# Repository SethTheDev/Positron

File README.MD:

# Resonance
An open-source USB-C Audio Interface powered by an STM32F411 and using a Cirrus Logic CS43198 DAC chip.

This is my magnum opus (*seriously*)

## Features
* STM32F411 microcontroller for USB audio
* Cirrus Logic CS43198 DAC with pseudo-differential output
* OPA1622 Differential Headphone Amplifier

## Rough Timeline
* (May 2026) - Raspberry Pi Pico + PCM5102

* (August 2026) - Stuck with the Pico because of it's versatility, however I decided to use a professional Cirrus Logic CS43198 chip
* (September 2026) - Switch to an STM32H743 (way too overpowered, what was I thinking), and included a CS5361 ADC with dual-channel op-amps for two mic inputs

* (October 2026) - Realized I would face a lot of power-related problems so I downgraded to an STM32F411 and kept only the CS43198 DAC. Also completely revamped the schematic so it would be easy to read

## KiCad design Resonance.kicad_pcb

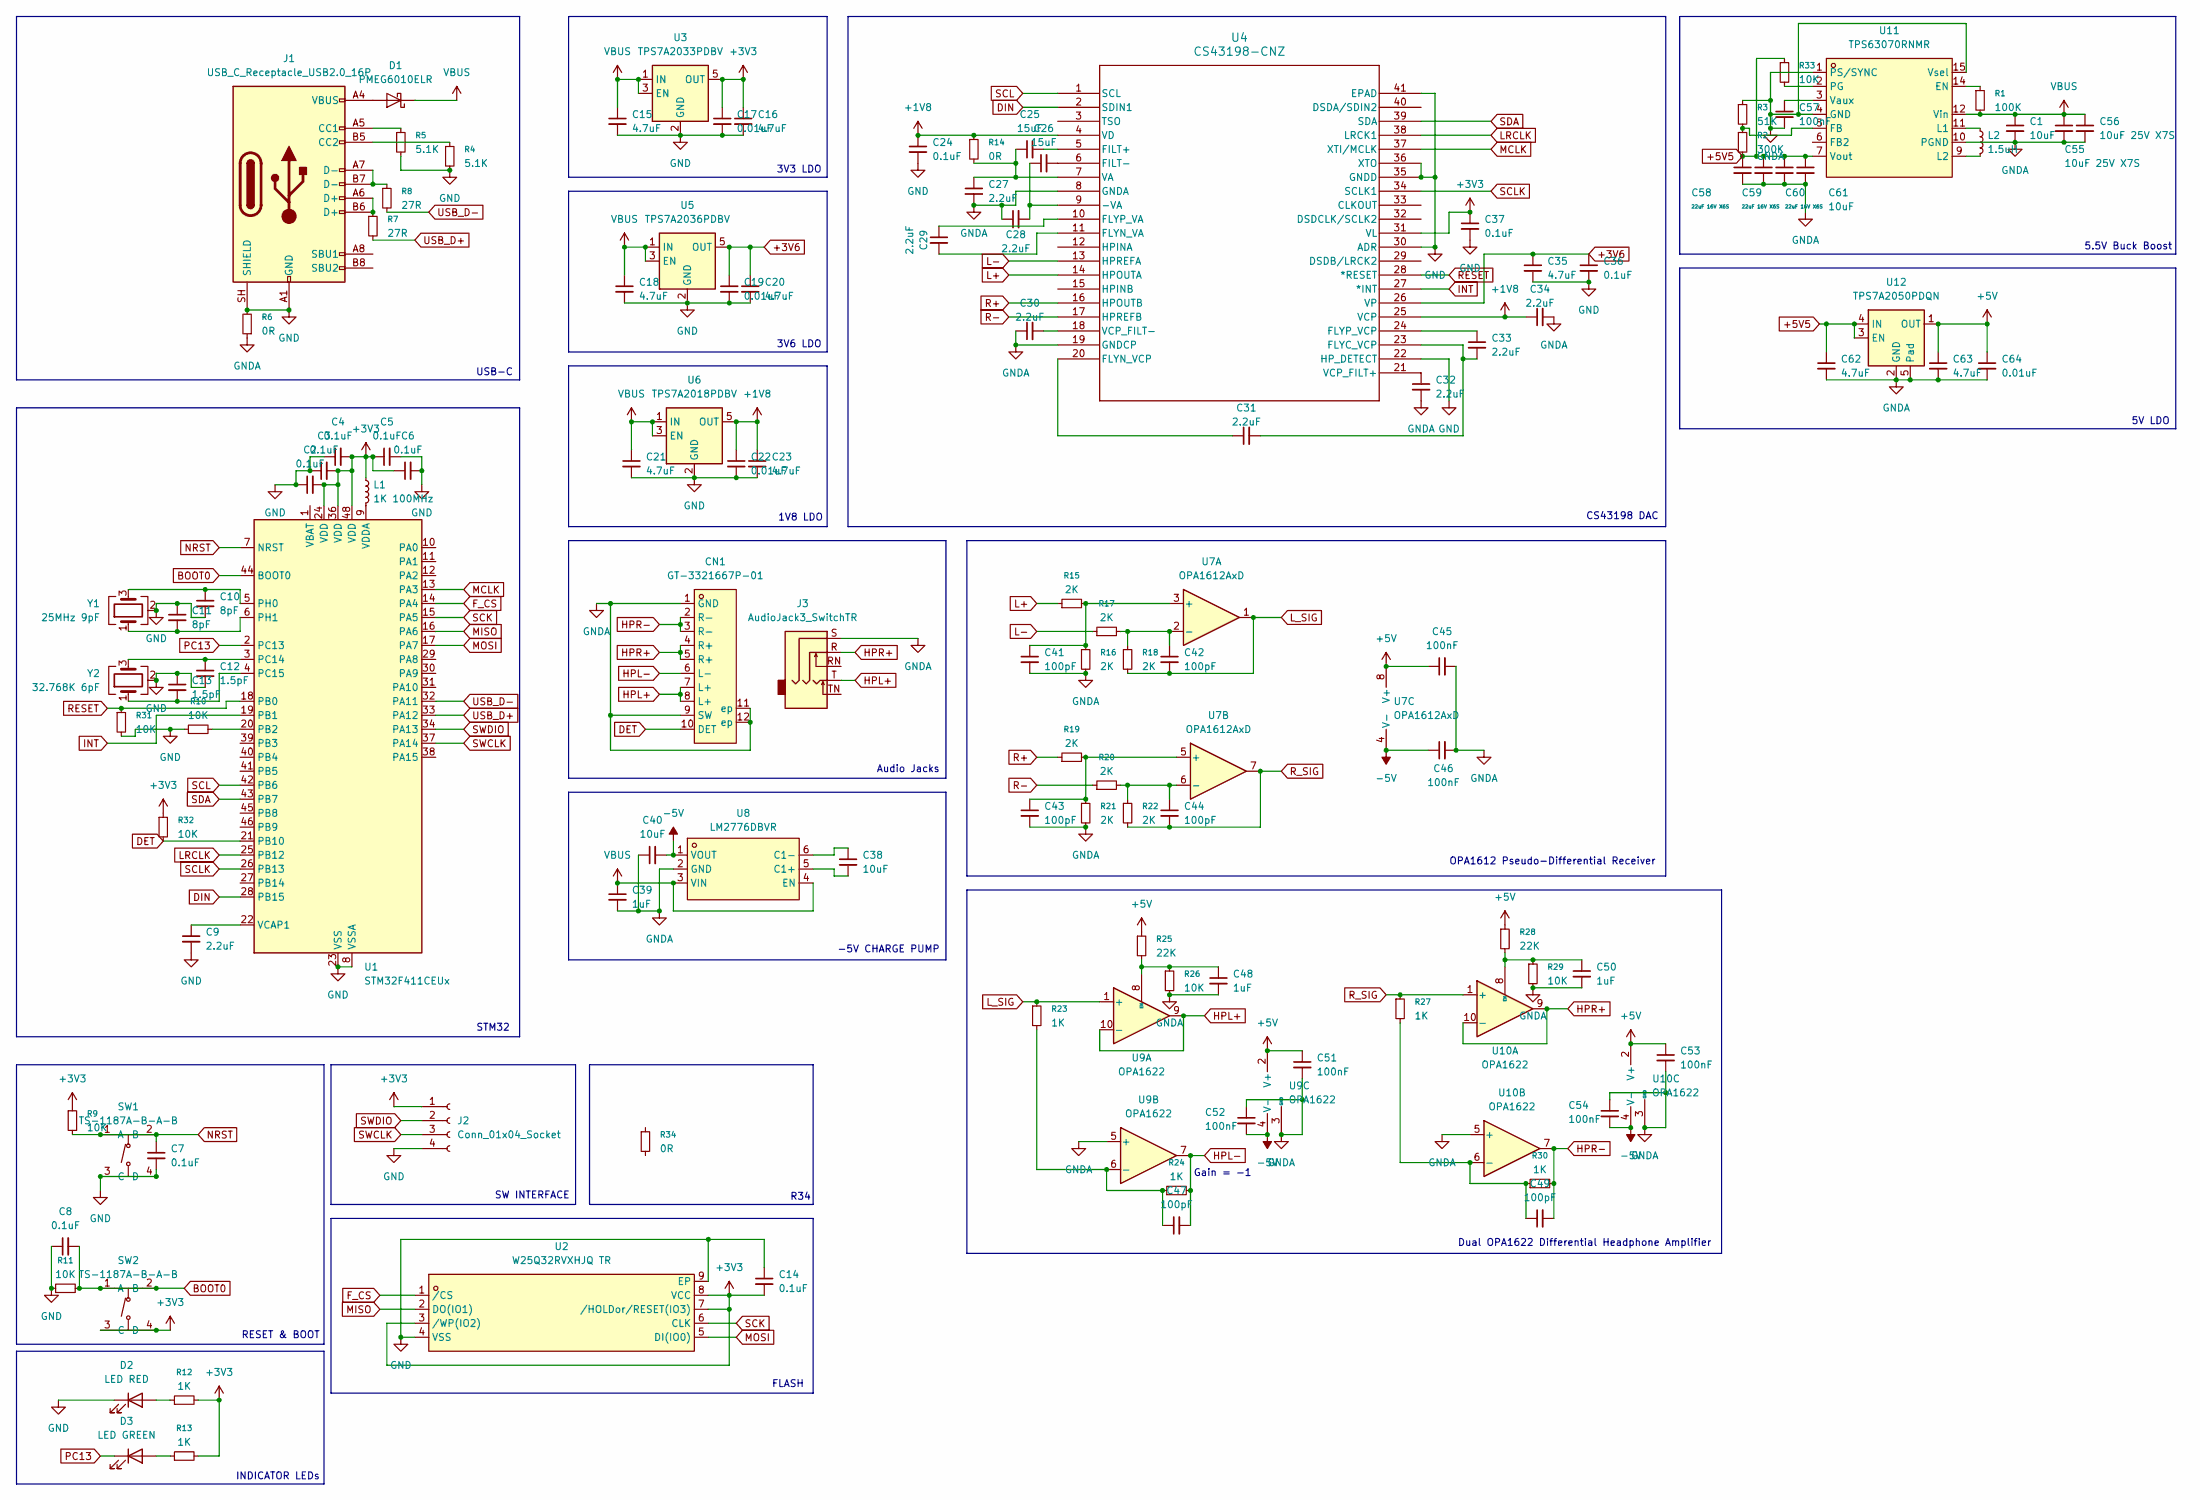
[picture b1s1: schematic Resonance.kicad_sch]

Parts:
C1, C61: 10uF; C_0603_1608Metric
C2, C3, C4, C5, C6, C7, C8, C14, C24, C36, C37: 0.1uF; C_0402_1005Metric
C9, C27, C28, C29, C30, C31, C32, C33, C34: 2.2uF; C_0402_1005Metric
C10, C11: 8pF; C_0402_1005Metric
C12, C13: 1.5pF; C_0402_1005Metric
C15, C16, C18, C20, C21, C23, C35, C62, C63: 4.7uF; C_0402_1005Metric
C17, C19, C22, C64: 0.01uF; C_0402_1005Metric
C25, C26: 15uF; C_0402_1005Metric
C38, C40: 10uF; C_0402_1005Metric
C39, C48, C50: 1uF; C_0402_1005Metric
C41, C42, C43, C44, C47, C49: 100pF; C_0402_1005Metric
C45, C46, C51, C52, C53, C54, C57: 100nF; C_0402_1005Metric
C55, C56: 10uF 25V X7S; C_0805_2012Metric
C58, C59, C60: 22uF 16V X6S; C_0805_2012Metric
CN1: GT-3321667P-01; AUDIO-TH_GT-3321667P-01; MPN GT-3321667P-01; LCSC Part C2762984
D1: PMEG6010ELR; Nexperia_CFP3_SOD-123W
D2: LED RED; LED_0805_2012Metric
D3: LED GREEN; LED_0805_2012Metric
J1: USB_C_Receptacle_USB2.0_16P; USB_C_Receptacle_GCT_USB4105-xx-A_16P_TopMnt_Horizontal
J2: Conn_01x04_Socket; PinSocket_1x04_P2.54mm_Vertical
J3: AudioJack3_SwitchTR; Jack_3.5mm_CUI_SJ1-3525N_Horizontal
L1: 1K 100MHz; L_0402_1005Metric
L2: 1.5uH; L_0402_1005Metric
R1: 100K; R_0402_1005Metric
R2: 300K; R_0402_1005Metric
R3: 51K; R_0402_1005Metric
R4, R5: 5.1K; R_0402_1005Metric
R6, R14, R34: 0R; R_0402_1005Metric
R7, R8: 27R; R_0402_1005Metric
R9, R10, R11, R26, R29, R31, R32, R33: 10K; R_0402_1005Metric
R12, R13, R23, R24, R27, R30: 1K; R_0402_1005Metric
R15, R16, R17, R18, R19, R20, R21, R22: 2K; R_0402_1005Metric
R25, R28: 22K; R_0402_1005Metric
SW1, SW2: TS-1187A-B-A-B; SW-SMD_4P-L5.1-W5.1-P3.70-LS6.5-TL_H1.5; MPN TS-1187A-B-A-B; LCSC Part C318884
U1: STM32F411CEUx; QFN-48-1EP_7x7mm_P0.5mm_EP5.6x5.6mm
U2: W25Q32RVXHJQ TR; USON-8_L3.0-W2.0-P0.50-BL-EP; MPN W25Q32RVXHJQ TR; LCSC Part C32246052
U3: TPS7A2033PDBV; SOT-23-5
U4: CS43198-CNZ; QFN_CS43198_CIR-M
U5: TPS7A2036PDBV; SOT-23-5
U6: TPS7A2018PDBV; SOT-23-5
U7: OPA1612AxD; SOIC-8_3.9x4.9mm_P1.27mm
U8: LM2776DBVR; SOT-23-6_L2.9-W1.6-P0.95-LS2.8-BR; MPN LM2776DBVR; LCSC Part C69527
U9, U10: OPA1622; Texas_S-PVSON-N10
U11: TPS63070RNMR; VQFN-15_L3.0-W2.5-P0.50-BL; MPN TPS63070RNMR; LCSC Part C109322
U12: TPS7A2050PDQN; Texas_X2SON-4_1x1mm_P0.65mm
Y1: 25MHz 9pF; Crystal_SMD_3225-4Pin_3.2x2.5mm
Y2: 32.768K 6pF; Crystal_SMD_3225-4Pin_3.2x2.5mm

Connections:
+1V8: C22.1, C23.1, C24.1, C34.1, R14.1, U4.4 (VD), U4.25 (VCP), U6.5 (OUT)
+3V3: C2.2, C3.2, C4.2, C5.1, C6.1, C14.2, C16.1, C17.1, C37.1, J2.1, L1.1, R9.1, R12.2, R13.2, R32.1, SW2.3 (C), SW2.4 (D), U1.24 (VDD), U1.36 (VDD), U1.48 (VDD), U2.3 (/WP(IO2)), U2.7 (/HOLDor/RESET(IO3)), U2.8 (VCC), U3.5 (OUT), U4.31 (VL)
+3V6: C19.1, C20.1, C35.1, C36.1, U4.26 (VP), U5.5 (OUT)
+5V: C45.1, C51.1, C53.1, C63.1, C64.1, R25.1, R28.1, U7.8 (V+), U9.2 (V+), U10.2 (V+), U12.1 (OUT)
+5V5: C58.1, C59.1, C60.1, C61.1, C62.1, R2.2, R33.1, U11.7 (Vout), U12.3 (EN), U12.4 (IN)
-5V: C40.2, C46.1, C52.2, C54.2, U7.4 (V-), U8.1 (VOUT), U9.4 (V-), U9.11 (V-), U10.4 (V-), U10.11 (V-)
BOOT0: C8.2, R11.2, SW2.1 (A), SW2.2 (B), U1.44 (BOOT0)
DET: CN1.10 (DET), R32.2, U1.21 (PB10)
DIN: U1.28 (PB15), U4.2 (SDIN1)
F_CS: U1.14 (PA4), U2.1 (/CS)
GND: C2.1, C3.1, C4.1, C5.2, C6.2, C7.2, C8.1, C9.2, C10.2, C11.1, C12.2, C13.1, C14.1, C15.2, C16.2, C17.2, C18.2, C19.2, C20.2, C21.2, C22.2, C23.2, C24.2, C35.2, C36.2, C37.2, D2.1 (K), J1.A1 (GND), J1.A12 (GND), J1.B1 (GND), J1.B12 (GND), J1.SH (SHIELD), J2.4, R4.2, R5.2, R6.2, R10.1, R11.1, R31.2, SW1.3 (C), SW1.4 (D), U1.8 (VSSA), U1.23 (VSS), U1.35 (VSS), U1.47 (VSS), U1.49 (VSS), U2.4 (VSS), U2.9 (EP), U3.2 (GND), U4.22 (HP_DETECT), U4.30 (ADR), U4.35 (GNDD), U4.36 (XTO), U4.41 (EPAD), U5.2 (GND), U6.2 (GND), Y1.2 (G), Y1.4 (G), Y2.2 (G), Y2.4 (G)
GNDA: C1.2, C27.2, C28.1, C30.1, C32.2, C34.2, C39.2, C40.1, C41.2, C43.2, C45.2, C46.2, C48.2, C50.2, C51.2, C52.1, C53.2, C54.1, C55.2, C56.2, C57.2, C58.2, C59.2, C60.2, C61.2, C62.2, C63.2, C64.2, CN1.1 (GND), CN1.9 (SW), CN1.11 (ep), CN1.12 (ep), J3.S, R3.1, R6.1, R16.2, R21.2, R26.2, R29.2, U4.8 (GNDA), U4.19 (GNDCP), U8.2 (GND), U9.3 (GND), U9.5 (+), U10.3 (GND), U10.5 (+), U11.1 (PS/SYNC), U11.4 (GND), U11.10 (PGND), U11.15 (Vsel), U12.2 (GND), U12.5 (Pad)
HPL+: CN1.7 (L+), CN1.8 (L+), J3.T, U9.9, U9.10 (-)
HPL-: C47.2, CN1.6 (L-), R24.2, U9.7
HPR+: CN1.4 (R+), CN1.5 (R+), J3.R, U10.9, U10.10 (-)
HPR-: C49.2, CN1.2 (R-), CN1.3 (R-), R30.2, U10.7
INT: U1.19 (PB1), U4.27 (*INT)
L+: R15.1, U4.14 (HPOUTA)
L-: R17.1, U4.13 (HPREFA)
LRCLK: U1.25 (PB12), U4.38 (LRCK1)
L_SIG: C42.2, R18.2, R23.1, U7.1, U9.1 (+)
MCLK: U1.13 (PA3), U4.37 (XTI/MCLK)
MISO: U1.16 (PA6), U2.2 (DO(IO1))
MOSI: U1.17 (PA7), U2.5 (DI(IO0))
NRST: C7.1, R9.2, SW1.1 (A), SW1.2 (B), U1.7 (NRST)
unnamed: D1.2 (A), J1.A4 (VBUS), J1.A9 (VBUS), J1.B4 (VBUS), J1.B9 (VBUS)
unnamed: D2.2 (A), R12.1
unnamed: D3.2 (A), R13.1
unnamed: J1.A5 (CC1), R5.1
unnamed: J1.B5 (CC2), R4.1
unnamed: J1.A6 (D+), J1.B6 (D+), R7.1
unnamed: J1.A7 (D-), J1.B7 (D-), R8.1
unnamed: R10.2, U1.20 (PB2)
unnamed: C12.1, U1.3 (PC14), Y2.3
unnamed: C13.2, U1.4 (PC15), Y2.1
unnamed: C10.1, U1.5 (PH0), Y1.3
unnamed: C11.2, U1.6 (PH1), Y1.1
unnamed: C9.1, U1.22 (VCAP1)
unnamed: L1.2, U1.9 (VDDA)
unnamed: C26.1, C28.2, U4.9 (-VA)
unnamed: C25.2, U4.5 (FILT+)
unnamed: C26.2, U4.6 (FILT-)
unnamed: C31.2, C33.2, U4.23 (FLYC_VCP)
unnamed: C29.2, U4.11 (FLYN_VA)
unnamed: C31.1, U4.20 (FLYN_VCP)
unnamed: C29.1, U4.10 (FLYP_VA)
unnamed: C33.1, U4.24 (FLYP_VCP)
unnamed: C25.1, C27.1, R14.2, U4.7 (VA)
unnamed: C32.1, U4.21 (VCP_FILT+)
unnamed: C30.2, U4.18 (VCP_FILT-)
unnamed: C41.1, R15.2, R16.1, U7.3 (+)
unnamed: C42.1, R17.2, R18.1, U7.2 (-)
unnamed: C43.1, R19.2, R21.1, U7.5 (+)
unnamed: C44.1, R20.2, R22.1, U7.6 (-)
unnamed: C38.2, U8.5 (C1+)
unnamed: C38.1, U8.6 (C1-)
unnamed: C48.1, R25.2, R26.1, U9.8 (EN)
unnamed: C47.1, R23.2, R24.1, U9.6 (-)
unnamed: C50.1, R28.2, R29.1, U10.8 (EN)
unnamed: C49.1, R27.2, R30.1, U10.6 (-)
unnamed: R1.1, U11.14 (EN)
unnamed: R2.1, R3.2, U11.5 (FB)
unnamed: L2.1, U11.11 (L1)
unnamed: L2.2, U11.9 (L2)
unnamed: R33.2, U11.2 (PG)
unnamed: C57.1, U11.3 (Vaux)
PC13: D3.1 (K), U1.2 (PC13)
R+: R19.1, U4.16 (HPOUTB)
R-: R20.1, U4.17 (HPREFB)
RESET: R31.1, U1.18 (PB0), U4.28 (*RESET)
R_SIG: C44.2, R22.2, R27.1, U7.7, U10.1 (+)
SCK: U1.15 (PA5), U2.6 (CLK)
SCL: U1.42 (PB6), U4.1 (SCL)
SCLK: U1.26 (PB13), U4.34 (SCLK1)
SDA: U1.43 (PB7), U4.39 (SDA)
SWCLK: J2.3, U1.37 (PA14)
SWDIO: J2.2, U1.34 (PA13)
USB_D+: R7.2, U1.33 (PA12)
USB_D-: R8.2, U1.32 (PA11)
VBUS: C1.1, C15.1, C18.1, C21.1, C39.1, C55.1, C56.1, D1.1 (K), R1.2, U3.1 (IN), U3.3 (EN), U5.1 (IN), U5.3 (EN), U6.1 (IN), U6.3 (EN), U8.3 (VIN), U8.4 (EN), U11.12 (Vin)

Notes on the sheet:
RESET & BOOT
STM32
FLASH
USB-C
Dual OPA1622 Differential Headphone Amplifier
INDICATOR LEDs
R34
CS43198 DAC
-5V CHARGE PUMP
5V LDO
SW INTERFACE
OPA1612 Pseudo-Differential Receiver
1V8 LDO
5.5V Buck Boost
Audio Jacks
Gain = -1
3V3 LDO
3V6 LDO

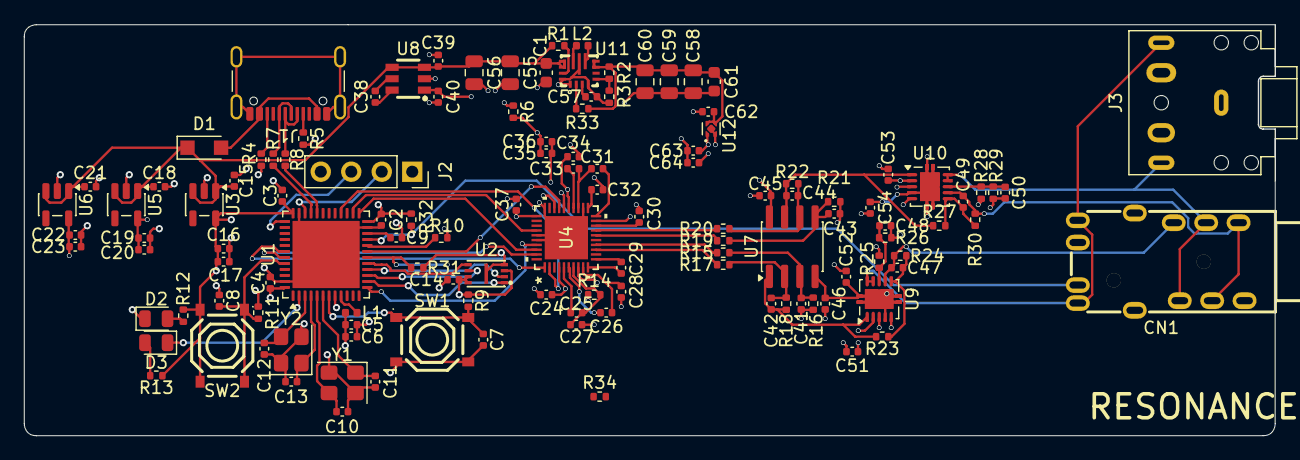
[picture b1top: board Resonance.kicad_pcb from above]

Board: 4 copper layers, 104.3 x 34.2 mm, 123 parts (0 on the bottom side), 80 nets.

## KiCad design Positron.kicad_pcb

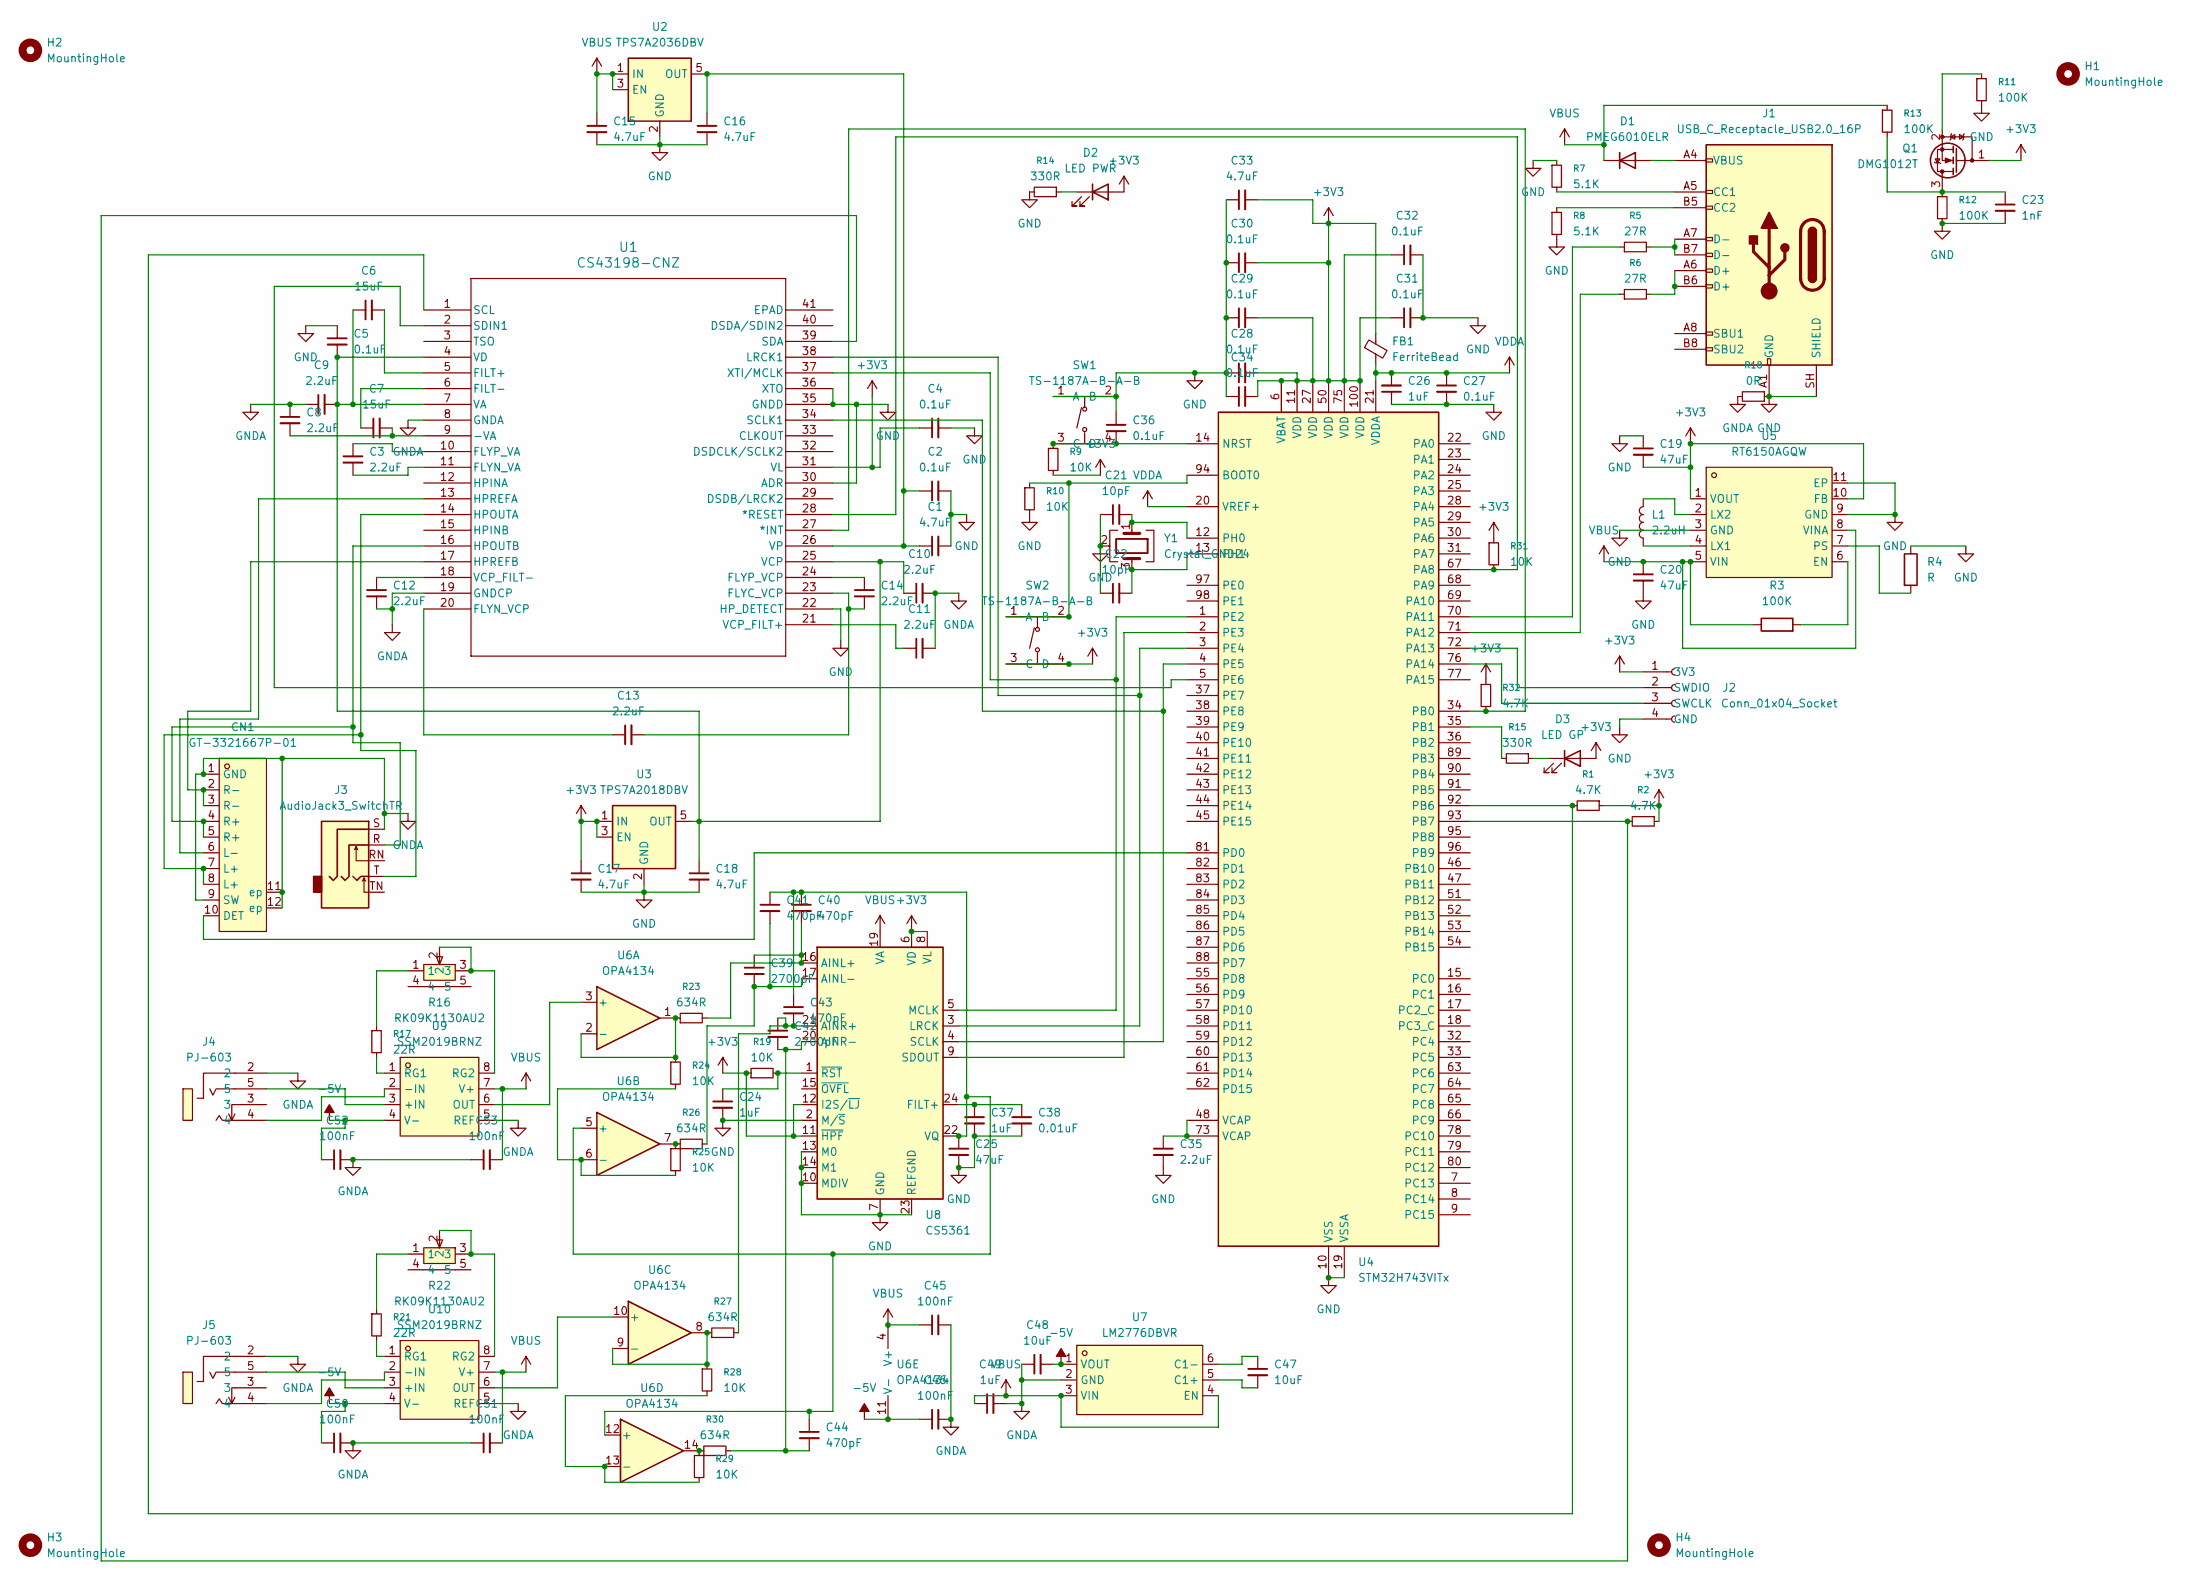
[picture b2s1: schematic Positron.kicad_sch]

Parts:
C1, C15, C16, C17, C18, C33: 4.7uF; C_0402_1005Metric
C2, C4, C5, C27, C28, C29, C30, C31, C32, C34, C36: 0.1uF; C_0402_1005Metric
C3, C8, C9, C10, C11, C12, C13, C14, C35: 2.2uF; C_0402_1005Metric
C6, C7: 15uF; C_0402_1005Metric
C19, C20, C25: 47uF; C_0402_1005Metric
C21, C22: 10pF; C_0402_1005Metric
C23: 1nF; C_0402_1005Metric
C24, C26, C37, C49: 1uF; C_0402_1005Metric
C38: 0.01uF; C_0402_1005Metric
C39, C42: 2700pF; C_0402_1005Metric
C40, C41, C43, C44: 470pF; C_0402_1005Metric
C45, C46, C50, C51, C52, C53: 100nF; C_0402_1005Metric
C47, C48: 10uF; C_0402_1005Metric
CN1: GT-3321667P-01; AUDIO-TH_GT-3321667P-01; MPN GT-3321667P-01; LCSC Part C2762984
D1: PMEG6010ELR; D_SOD-123
D2: LED PWR; LED_0805_2012Metric
D3: LED GP; LED_0805_2012Metric
FB1: FerriteBead; L_0402_1005Metric
H1, H2, H3, H4: MountingHole; MountingHole_2.2mm_M2
J1: USB_C_Receptacle_USB2.0_16P; USB_C_Receptacle_GCT_USB4105-xx-A_16P_TopMnt_Horizontal
J2: Conn_01x04_Socket; PinHeader_1x04_P2.54mm_Vertical
J3: AudioJack3_SwitchTR; Jack_3.5mm_CUI_SJ1-3525N_Horizontal
J4, J5: PJ-603; AUDIO-TH_PJ-603; MPN PJ-603环保; LCSC Part C309272
L1: 2.2uH; L_0402_1005Metric
Q1: DMG1012T; SOT-523
R1, R2, R32: 4.7K; R_0402_1005Metric
R3, R11, R12, R13: 100K; R_0402_1005Metric
R4: R; R_0402_1005Metric
R5, R6: 27R; R_0402_1005Metric
R7, R8: 5.1K; R_0402_1005Metric
R9, R10, R19, R24, R25, R28, R29, R31: 10K; R_0402_1005Metric
R14, R15: 330R; R_0402_1005Metric
R16, R22: RK09K1130AU2; RES-ADJ-TH_RK09K1130AJ3; MPN RK09K1130AU2; LCSC Part C388855
R17, R21: 22R; R_0402_1005Metric
R18: 0R; R_0402_1005Metric
R23, R26, R27, R30: 634R; R_0402_1005Metric
SW1, SW2: TS-1187A-B-A-B; SW-SMD_4P-L5.1-W5.1-P3.70-LS6.5-TL_H1.5; MPN TS-1187A-B-A-B; LCSC Part C318884
U1: CS43198-CNZ; QFN_CS43198_CIR
U2: TPS7A2036DBV; SOT-23-5
U3: TPS7A2018DBV; SOT-23-5
U4: STM32H743VITx; LQFP-100_14x14mm_P0.5mm
U5: RT6150AGQW; WDFN-10_L3.0-W3.0-P0.50-BL-EP; MPN RT6150AGQW; LCSC Part C147971
U6: OPA4134; SOIC-14_3.9x8.7mm_P1.27mm
U7: LM2776DBVR; SOT-23-6_L2.9-W1.6-P0.95-LS2.8-BR; MPN LM2776DBVR; LCSC Part C69527
U8: CS5361; TSSOP-24_4.4x7.8mm_P0.65mm
U9, U10: SSM2019BRNZ; SOIC-8_L5.0-W4.0-P1.27-LS6.0-BL; MPN SSM2019BRNZ; LCSC Part C691044
Y1: Crystal_GND24; Crystal_SMD_3225-4Pin_3.2x2.5mm

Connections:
+3V3: C4.1, C17.1, C19.2, C28.2, C29.2, C30.2, C31.1, C32.1, C33.2, C34.2, D2.2 (A), D3.2 (A), FB1.1, J2.1 (3V3), Q1.1 (G), R1.1, R2.1, R9.2, R19.1, R31.1, R32.1, SW2.3 (C), SW2.4 (D), U1.31 (VL), U3.1 (IN), U3.3 (EN), U4.6 (VBAT), U4.11 (VDD), U4.27 (VDD), U4.50 (VDD), U4.75 (VDD), U4.100 (VDD), U5.1 (VOUT), U5.10 (FB), U8.6 (VD), U8.8 (VL), U8.11 (~HPF), U8.12 (I2S/~LJ)
-5V: C46.1, C48.2, C50.1, C52.1, U6.11 (V-), U7.1 (VOUT), U9.4 (V-), U10.4 (V-)
GND: C1.2, C2.2, C4.2, C5.1, C15.2, C16.2, C17.2, C18.2, C19.1, C20.2, C21.1, C22.1, C23.2, C24.2, C25.2, C26.1, C27.2, C28.1, C29.1, C30.1, C31.2, C32.2, C33.1, C34.1, C35.2, C36.1, C37.2, C38.2, J1.A1 (GND), J1.A12 (GND), J1.B1 (GND), J1.B12 (GND), J1.SH (SHIELD), J2.4 (GND), R4.1, R7.1, R8.2, R10.2, R11.2, R12.2, R14.2, R18.1, SW1.1 (A), SW1.2 (B), U1.22 (HP_DETECT), U1.30 (ADR), U1.35 (GNDD), U1.36 (XTO), U2.2 (GND), U3.2 (GND), U4.10 (VSS), U4.19 (VSSA), U4.26 (VSS), U4.49 (VSS), U4.74 (VSS), U4.99 (VSS), U5.3 (GND), U5.9 (GND), U5.11 (EP), U8.2 (M/~S), U8.7 (GND), U8.10 (MDIV), U8.13 (M0), U8.14 (M1), U8.18 (GND), U8.23 (REFGND), Y1.2 (G), Y1.4 (G)
GNDA: C8.1, C9.1, C10.2, C11.2, C12.2, C45.2, C46.2, C48.1, C49.2, C50.2, C51.1, C52.2, C53.1, CN1.1 (GND), CN1.9 (SW), CN1.11 (ep), CN1.12 (ep), J3.S, J4.2, J5.2, R18.2, U1.8 (GNDA), U1.19 (GNDCP), U7.2 (GND), U9.5 (REF), U10.5 (REF)
unnamed: C35.1, U4.48 (VCAP), U4.73 (VCAP)
unnamed: CN1.10 (DET), U4.81 (PD0)
unnamed: CN1.6 (L-), U1.13 (HPREFA)
unnamed: D1.2 (A), J1.A4 (VBUS), J1.A9 (VBUS), J1.B4 (VBUS), J1.B9 (VBUS)
unnamed: D2.1 (K), R14.1
unnamed: D3.1 (K), R15.1
unnamed: J1.A5 (CC1), R7.2
unnamed: J1.B5 (CC2), R8.1
unnamed: J1.A6 (D+), J1.B6 (D+), R6.2
unnamed: J1.A7 (D-), J1.B7 (D-), R5.2
unnamed: J2.3 (SWCLK), U4.76 (PA14)
unnamed: J2.2 (SWDIO), U4.72 (PA13)
unnamed: C23.1, Q1.3 (D), R12.1, R13.2
unnamed: Q1.2 (S), R11.1
unnamed: R16.1, R17.1
unnamed: R21.1, R22.1
unnamed: R25.1, R26.1, U6.7
unnamed: R29.1, R30.1, U6.14
unnamed: C36.2, R9.1, SW1.3 (C), SW1.4 (D), U4.14 (NRST)
unnamed: R10.1, SW2.1 (A), SW2.2 (B), U4.94 (BOOT0)
unnamed: R32.2, U1.27 (*INT), U4.34 (PB0)
unnamed: R31.2, U1.28 (*RESET), U4.67 (PA8)
unnamed: C7.2, C8.2, U1.9 (-VA)
unnamed: C6.2, U1.5 (FILT+)
unnamed: C7.1, U1.6 (FILT-)
unnamed: C13.2, C14.2, U1.23 (FLYC_VCP)
unnamed: C3.2, U1.11 (FLYN_VA)
unnamed: C13.1, U1.20 (FLYN_VCP)
unnamed: C3.1, U1.10 (FLYP_VA)
unnamed: C14.1, U1.24 (FLYP_VCP)
unnamed: CN1.7 (L+), CN1.8 (L+), J3.T, U1.14 (HPOUTA)
unnamed: CN1.4 (R+), CN1.5 (R+), J3.R, U1.16 (HPOUTB)
unnamed: CN1.2 (R-), CN1.3 (R-), U1.17 (HPREFB)
unnamed: U1.38 (LRCK1), U4.3 (PE4), U8.3 (LRCK)
unnamed: R1.2, U1.1 (SCL), U4.92 (PB6)
unnamed: U1.34 (SCLK1), U4.4 (PE5), U8.4 (SCLK)
unnamed: R2.2, U1.39 (SDA), U4.93 (PB7)
unnamed: U1.2 (SDIN1), U4.5 (PE6)
unnamed: C5.2, C6.1, C9.2, C10.1, C18.1, U1.4 (VD), U1.7 (VA), U1.25 (VCP), U3.5 (OUT)
unnamed: C11.1, U1.21 (VCP_FILT+)
unnamed: C12.1, U1.18 (VCP_FILT-)
unnamed: C1.1, C2.1, C16.1, U1.26 (VP), U2.5 (OUT)
unnamed: U1.37 (XTI/MCLK), U4.1 (PE2), U8.5 (MCLK)
unnamed: R5.1, U4.70 (PA11)
unnamed: R6.1, U4.71 (PA12)
unnamed: R15.2, U4.35 (PB1)
unnamed: U4.2 (PE3), U8.9 (SDOUT)
unnamed: C21.2, U4.12 (PH0), Y1.1
unnamed: C22.2, U4.13 (PH1), Y1.3
unnamed: R3.2, U5.6 (EN)
unnamed: L1.1, U5.4 (LX1)
unnamed: L1.2, U5.2 (LX2)
unnamed: R4.2, U5.7 (PS)
unnamed: U6.3 (+), U9.6 (OUT)
unnamed: R23.1, R24.1, U6.1, U6.2 (-)
unnamed: C25.1, C40.1, C41.1, C43.1, C44.1, U6.5 (+), U6.12 (+), U8.22 (VQ)
unnamed: R24.2, R25.2, U6.6 (-)
unnamed: R27.1, R28.1, U6.8, U6.9 (-)
unnamed: R28.2, R29.2, U6.13 (-)
unnamed: C47.2, U7.5 (C1+)
unnamed: C47.1, U7.6 (C1-)
unnamed: C39.1, C40.2, R23.2, U8.16 (AINL+)
unnamed: C39.2, C41.2, R26.2, U8.17 (AINL-)
unnamed: C42.1, C43.2, R27.2, U8.21 (AINR+)
unnamed: C42.2, C44.2, R30.2, U8.20 (AINR-)
unnamed: C37.1, C38.1, U8.24 (FILT+)
unnamed: C24.1, R19.2, U8.1 (~RST)
unnamed: J4.5, U9.3 (+IN)
unnamed: J4.4, U9.2 (-IN)
unnamed: R17.2, U9.1 (RG1)
unnamed: R16.2, R16.3, U9.8 (RG2)
unnamed: J5.5, U10.3 (+IN)
unnamed: J5.4, U10.2 (-IN)
unnamed: U6.10 (+), U10.6 (OUT)
unnamed: R21.2, U10.1 (RG1)
unnamed: R22.2, R22.3, U10.8 (RG2)
VBUS: C15.1, C20.1, C45.1, C49.1, C51.2, C53.2, D1.1 (K), R3.1, R13.1, U2.1 (IN), U2.3 (EN), U5.5 (VIN), U5.8 (VINA), U6.4 (V+), U7.3 (VIN), U7.4 (EN), U8.19 (VA), U9.7 (V+), U10.7 (V+)
VDDA: C26.2, C27.1, FB1.2, U4.20 (VREF+), U4.21 (VDDA)

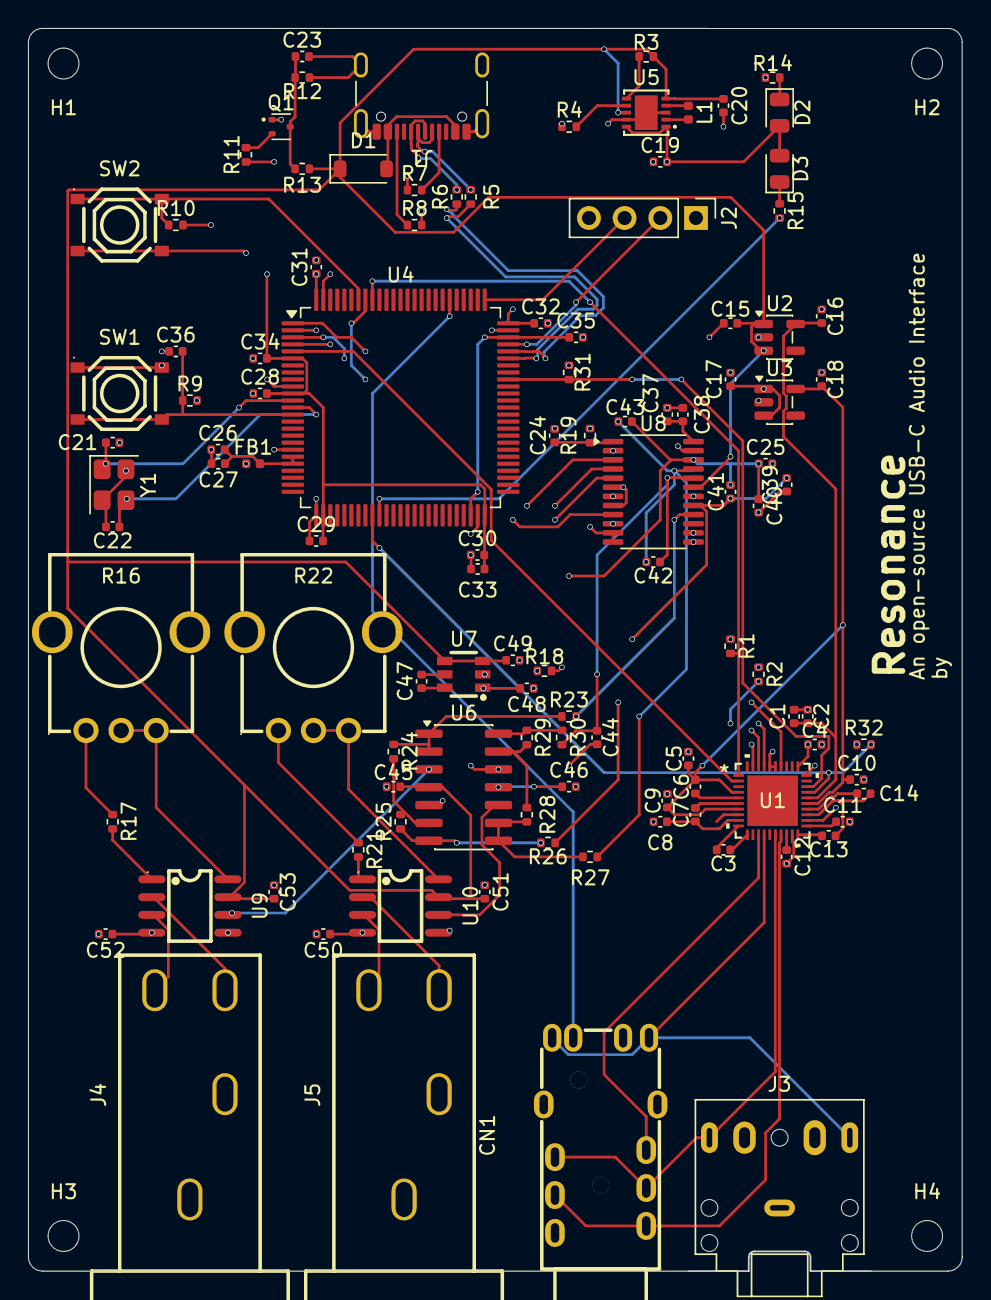
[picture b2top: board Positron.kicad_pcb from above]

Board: 4 copper layers, 66.5 x 88.5 mm, 113 parts (0 on the bottom side), 82 nets.
